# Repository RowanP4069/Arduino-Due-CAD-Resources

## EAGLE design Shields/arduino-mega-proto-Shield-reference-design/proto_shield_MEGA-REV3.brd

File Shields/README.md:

**CAD resources relating to Arduino Due shields**

*arduino-mega-proto-Shield-reference-design* - product drawings by Arduino.cc in Autodesk Eagle/Fusion360 format retreived from https://store-usa.arduino.cc/products/arduino-mega-proto-shield-rev3-pcb 2022-04-09.

*DUELib130425.lbr* - an Autocad part library by cowasaki in Autodesk Eagle/Fusion360 format retreived from https://forum.arduino.cc/t/due-shield-eagle-file/150210 2022-04-09

*Blank Shield (from mega shield)* - depopluated versions of the arduino-mega-proto-Shield in Fusion360 and Eagle board formats.

*Blank Shield (from Due)* - a depopulated version of the Arduino Due board intended as a starting point for shield design. In Fusion360 and Eagle formats.

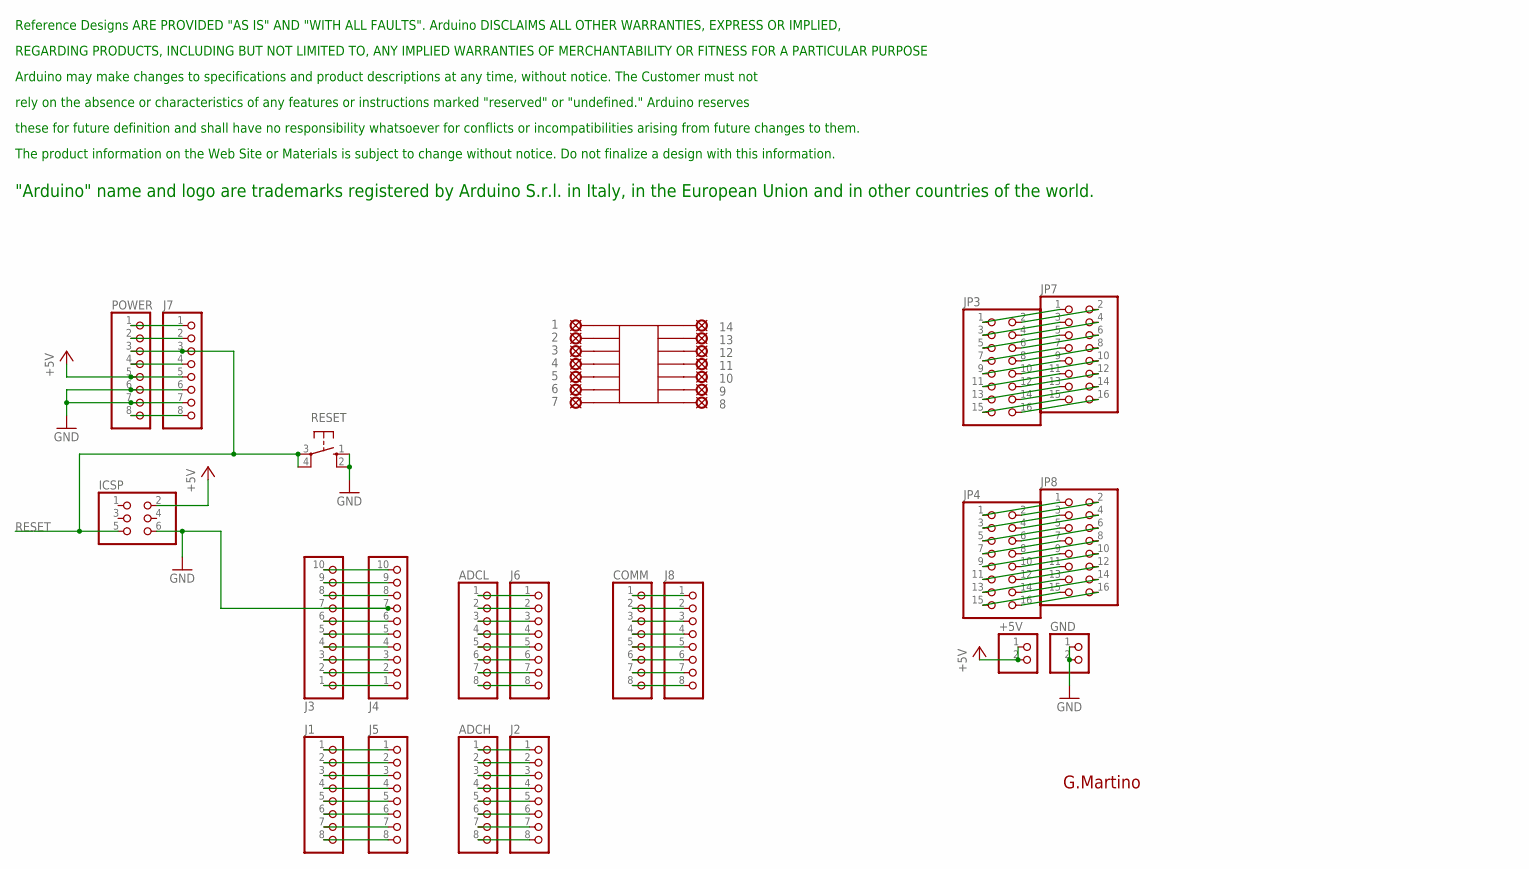
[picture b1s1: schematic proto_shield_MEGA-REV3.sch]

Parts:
1, 2, 3, 4, 5, 6, 7, 8, 9, 10, 11, 12, 13, 14: LSP10
+5V: PINHD-1X2; 1X02
ADCH: PINHD-1X8TH; 1X08-TH
ADCL: PINHD-1X8TH; 1X08-TH
COMM: PINHD-1X8TH; 1X08-TH
GND: PINHD-1X2; 1X02
IC2: SMD-14; SO-14NMW
ICSP: PINHD-2X3; 2X03
J1, J2, J5, J6, J7, J8: PINHD-1X8TH; 1X08-TH
J3, J4: PINHD-1X10TH; 1X10-TH
JP3, JP4, JP7, JP8: PINHD-2X8; 2X08
POWER: PINHD-1X8TH; 1X08-TH
RESET: 10-XX; B3F-10XX
U$1: DISCLAIMER_MINI; DISCLAIMER

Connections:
+5V: +5V.1, +5V.2, ICSP.2, J7.5, POWER.5
+9V: J7.8, POWER.8
GND: GND.1, GND.2, ICSP.6, J3.7, J4.7, J7.6, J7.7, POWER.6, POWER.7, RESET.1 (S), RESET.2 (S1)
unnamed: J3.1, J4.1
unnamed: J3.6, J4.6
unnamed: J3.4, J4.4
unnamed: J3.2, J4.2
unnamed: J3.3, J4.3
unnamed: J1.1, J5.1
unnamed: J1.2, J5.2
unnamed: J1.3, J5.3
unnamed: J1.4, J5.4
unnamed: J1.5, J5.5
unnamed: J1.6, J5.6
unnamed: J1.7, J5.7
unnamed: J1.8, J5.8
unnamed: ADCL.1, J6.1
unnamed: ADCL.2, J6.2
unnamed: ADCL.3, J6.3
unnamed: ADCL.4, J6.4
unnamed: ADCL.5, J6.5
unnamed: ADCL.6, J6.6
unnamed: 14.MP, IC2.P$14
unnamed: ADCL.7, J6.7
unnamed: ADCL.8, J6.8
unnamed: ADCH.1, J2.1
unnamed: ADCH.2, J2.2
unnamed: ADCH.3, J2.3
unnamed: 13.MP, IC2.P$13
unnamed: 12.MP, IC2.P$12
unnamed: 11.MP, IC2.P$11
unnamed: 10.MP, IC2.P$10
unnamed: 9.MP, IC2.P$9
unnamed: 8.MP, IC2.P$8
unnamed: 7.MP, IC2.P$7
unnamed: 6.MP, IC2.P$6
unnamed: 5.MP, IC2.P$5
unnamed: 3.MP, IC2.P$3
unnamed: 2.MP, IC2.P$2
unnamed: 1.MP, IC2.P$1
unnamed: 4.MP, IC2.P$4
unnamed: ADCH.4, J2.4
unnamed: ADCH.5, J2.5
unnamed: ADCH.6, J2.6
unnamed: J7.4, POWER.4
unnamed: J3.9, J4.9
unnamed: ADCH.7, J2.7
unnamed: ADCH.8, J2.8
unnamed: COMM.1, J8.1
unnamed: COMM.2, J8.2
unnamed: COMM.3, J8.3
unnamed: COMM.4, J8.4
unnamed: COMM.5, J8.5
unnamed: COMM.6, J8.6
unnamed: COMM.7, J8.7
unnamed: COMM.8, J8.8
unnamed: J3.5, J4.5
unnamed: JP3.1, JP7.1
unnamed: JP3.2, JP7.2
unnamed: JP3.3, JP7.3
unnamed: JP3.4, JP7.4
unnamed: JP3.5, JP7.5
unnamed: JP3.6, JP7.6
unnamed: JP3.7, JP7.7
unnamed: JP3.8, JP7.8
unnamed: JP3.9, JP7.9
unnamed: JP3.10, JP7.10
unnamed: JP3.11, JP7.11
unnamed: JP3.12, JP7.12
unnamed: JP3.13, JP7.13
unnamed: JP3.14, JP7.14
unnamed: JP3.15, JP7.15
unnamed: JP3.16, JP7.16
unnamed: JP4.1, JP8.1
unnamed: JP4.2, JP8.2
unnamed: JP4.3, JP8.3
unnamed: JP4.4, JP8.4
unnamed: JP4.5, JP8.5
unnamed: JP4.6, JP8.6
unnamed: JP4.7, JP8.7
unnamed: JP4.8, JP8.8
unnamed: JP4.9, JP8.9
unnamed: JP4.10, JP8.10
unnamed: JP4.11, JP8.11
unnamed: JP4.12, JP8.12
unnamed: JP4.13, JP8.13
unnamed: JP4.14, JP8.14
unnamed: JP4.15, JP8.15
unnamed: JP4.16, JP8.16
unnamed: J7.2, POWER.2
unnamed: J7.1, POWER.1
unnamed: J3.8, J4.8
unnamed: J3.10, J4.10
RESET: ICSP.5, J7.3, POWER.3, RESET.3, RESET.4 (P1)

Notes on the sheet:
G.Martino

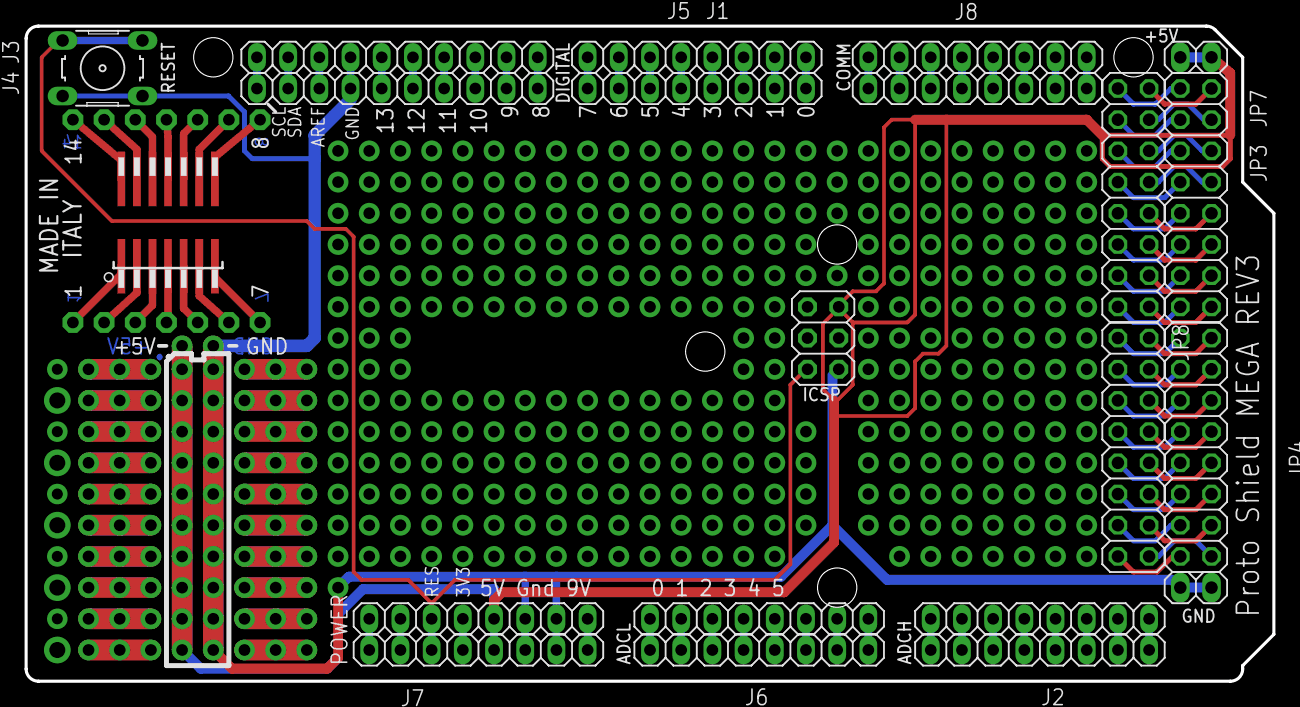
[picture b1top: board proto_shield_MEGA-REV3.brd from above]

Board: 2 copper layers, 101.6 x 53.3 mm, 36 parts (0 on the bottom side), 94 nets.

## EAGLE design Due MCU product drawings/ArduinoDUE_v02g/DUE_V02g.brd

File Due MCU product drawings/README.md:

**CAD resources related to the Due MCU**

*ArduinoDUE_v02g* - the Arduino Due MCU product drawings by Arduino.cc in Autodesk Eagle/Fusion360 format retreived from https://store-usa.arduino.cc/products/arduino-due 2022-04-09.

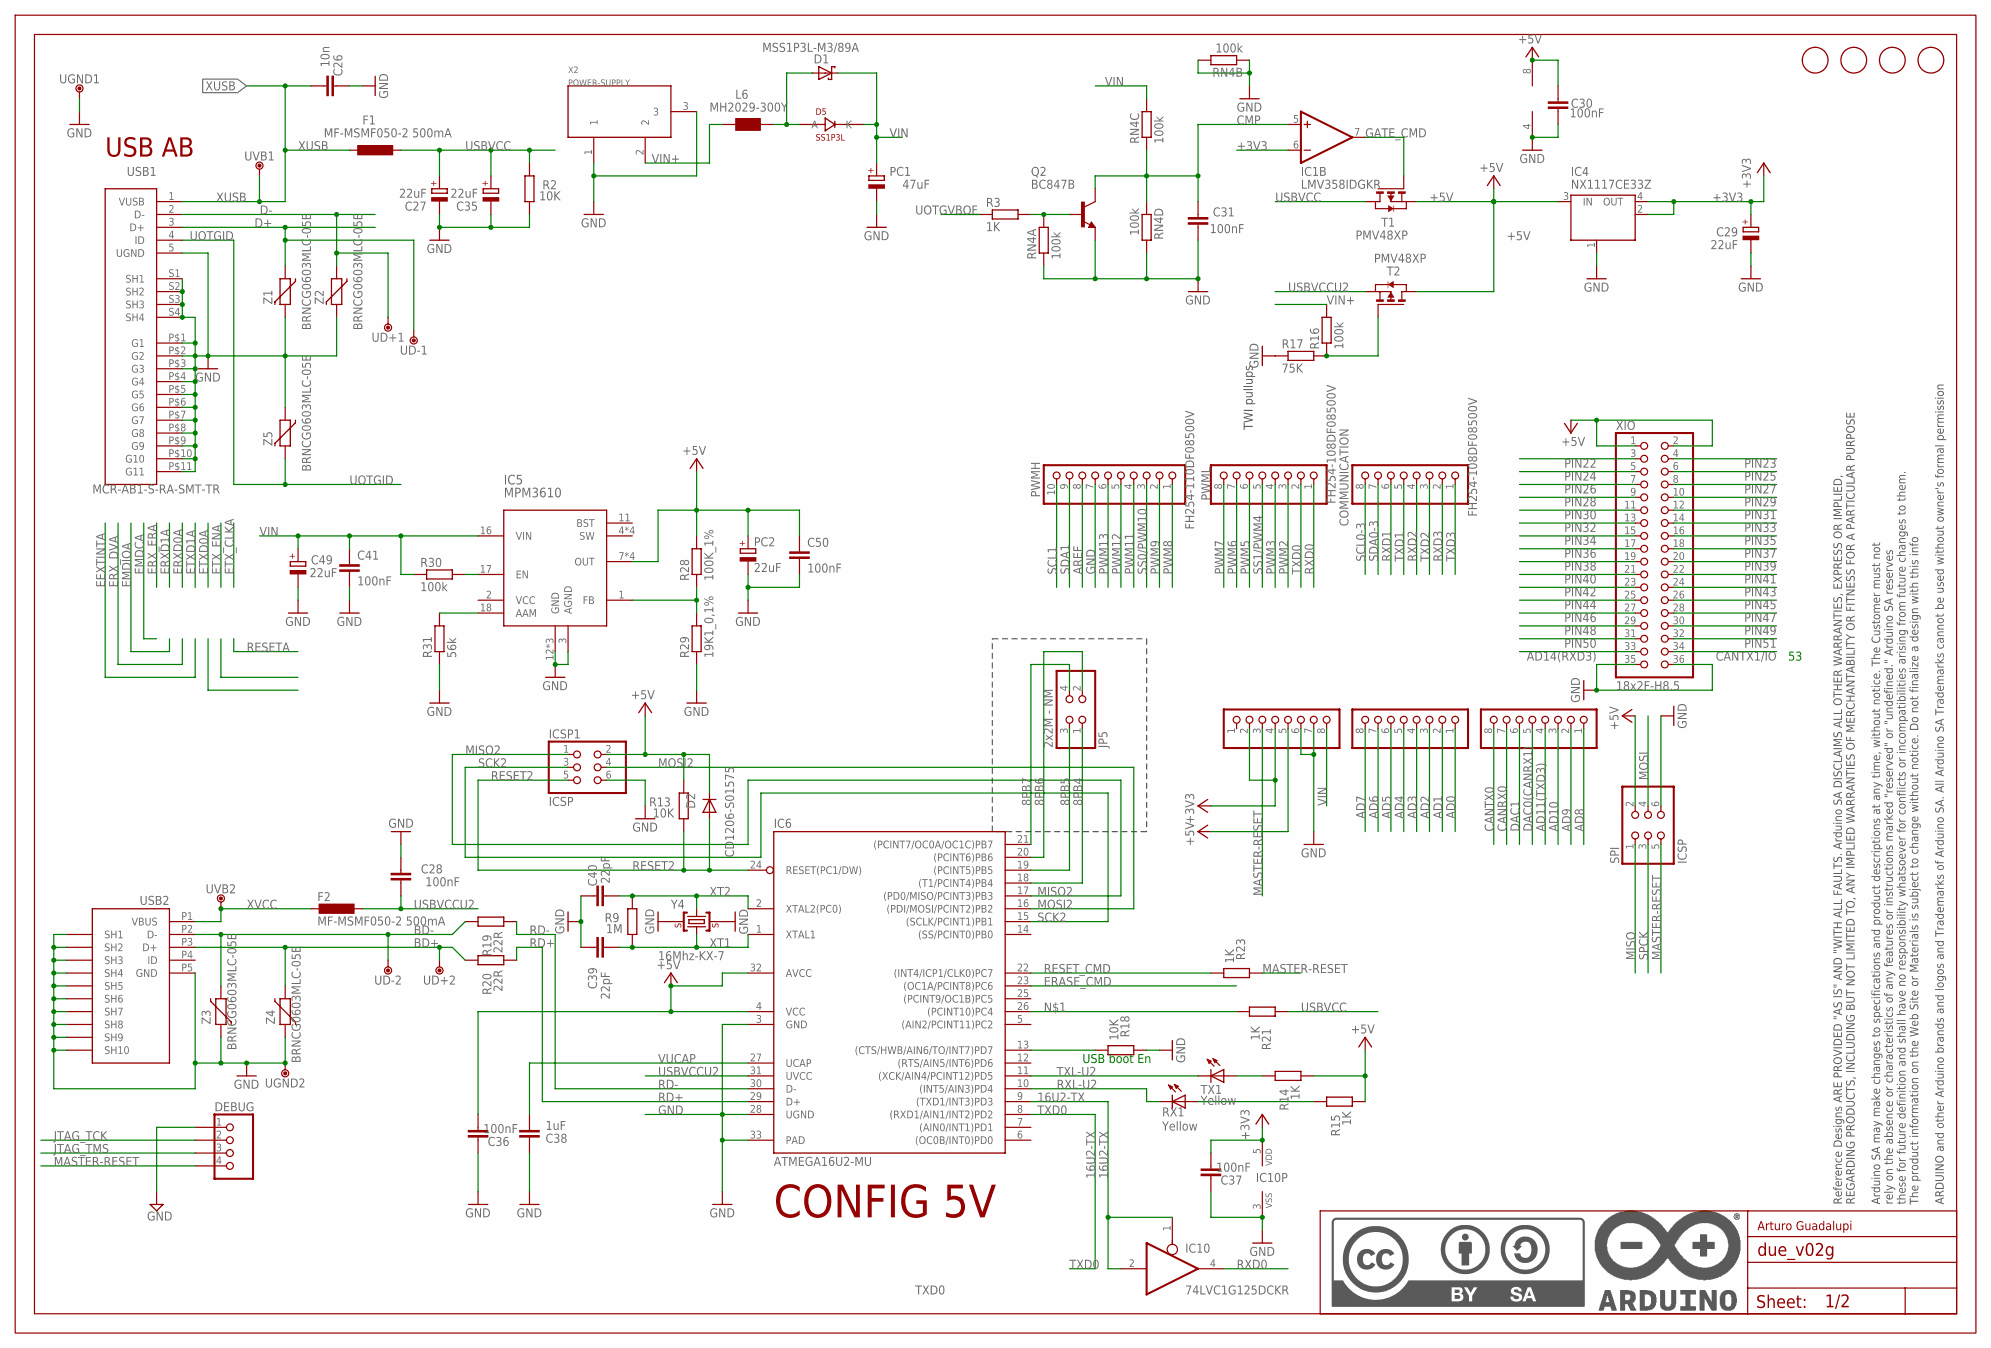
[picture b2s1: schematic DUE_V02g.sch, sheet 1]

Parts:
ADCH: FH254-108DF08500V; 1X08
ADCL: FH254-108DF08500V; 1X08
C26: 10n; C0402
C27, C29, C35, C49: 22uF; SMC_B
C28, C30, C31, C36, C37: 100nF; C0402
C38: 1uF; C0402
C39, C40: 22pF; C0402
C41, C50: 100nF; C0603-ROUND
COMMUNICATION: FH254-108DF08500V; 1X08
D1: MSS1P3L-M3/89A; MICROSMP
D2: CD1206-S01575; MINIMELF
D5: SS1P3L; DO220AAL
DEBUG: 0644_4X1VP.2,54H11,8; PH1X4-THT
F1, F2: MF-MSMF050-2 500mA; L1812
FID1, FID2, FID3, FID4: FIDUCIALMOUNT; FIDUCIA-MOUNT
IC1: LMV358IDGKR; MSOP08
IC4: NX1117CE33Z; SOT223
IC5: MPM3610; QFN-20
IC6: ATMEGA16U2-MU; MLF32
IC10: 74LVC1G125DCKR; SC70-5
ICSP1: ICSP; 2X03
JP5: 2x2M - NM; 2X02
L6: MH2029-300Y; 0805
PC1: 47uF; PANASONIC_D
PC2: 22uF; SMC_B
POWER: FH254-108DF08500V; 1X08
PWMH: FH254-110DF08500V; 1X10
PWML: FH254-108DF08500V; 1X08
Q2: BC847B; SOT23
R2, R13, R18: 10K; R0402
R3, R14, R15, R21, R23: 1K; R0402
R9: 1M; R0402
R16: 100k; R0402
R17: 75K; R0603-ROUND
R19, R20: 22R; R0402
R28: 100K_1%; R0603-ROUND
R29: 19K1_0,1%; R0603-ROUND
R30: 100k; R0603-ROUND
R31: 56k; R0603-ROUND
RN4: 100k; CAY16
RX1: Yellow; CHIPLED_0805
SPI: ICSP; 2X03
T1, T2: PMV48XP; SOT-23
TX1: Yellow; CHIPLED_0805
U$1: DNP; FRAME
UD+1, UD+2: DNP; TP-1.00MM
UD-1, UD-2: DNP; TP-1.00MM
UGND1, UGND2: DNP; TP-1.00MM
USB1: MCR-AB1-S-RA-SMT-TR; MCR-AB1-S-RA-SMT
USB2: MCR-B-S-RA-SMT-CS1TR; CON2_USB_MICRO_B_AT
UVB1, UVB2: DNP; TP-1.00MM
X2: POWER-SUPPLY; POWERSUPPLY_DC-21MM
XIO: 18x2F-H8.5; 2X18
Y4: 16Mhz-KX-7; CRYSTAL-3.2-2.5
Z1, Z2, Z3, Z4, Z5: BRNCG0603MLC-05E; CT/CN0603

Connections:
8PB4: IC6.18 ((T1/PCINT4)PB4), JP5.1
8PB5: IC6.19 ((PCINT5)PB5), JP5.3
8PB6: IC6.20 ((PCINT6)PB6), JP5.2
8PB7: IC6.21 ((PCINT7/OC0A/OC1C)PB7), JP5.4
16U2-TX: IC6.9 ((TXD1/INT3)PD3), IC10.1 (OE), IC10.2 (I)
+3V3: C29.+, C37.1, IC1.6 (-IN), IC4.2 (OUT), IC4.4 (OUT), IC10.5 (VDD), POWER.2, POWER.4; also elsewhere on the board
+5V: C30.2, C36.1, C50.1, D2.C, IC1.8 (V+), IC4.3 (IN), IC5.7 (OUT), IC5.8 (OUT), IC5.9 (OUT), IC5.20 (OUT), IC6.4 (VCC), IC6.32 (AVCC), ICSP1.2, PC2.+, POWER.5, R13.2, R14.1, R15.1, R28.2, SPI.2, T1.2 (S), T2.1 (D), XIO.1, XIO.2
AD0: ADCL.1; also elsewhere on the board
AD1: ADCL.2; also elsewhere on the board
AD2: ADCL.3; also elsewhere on the board
AD3: ADCL.4; also elsewhere on the board
AD4: ADCL.5; also elsewhere on the board
AD5: ADCL.6; also elsewhere on the board
AD6: ADCL.7; also elsewhere on the board
AD7: ADCL.8; also elsewhere on the board
AD8: ADCH.1; also elsewhere on the board
AD9: ADCH.2; also elsewhere on the board
AD10: ADCH.3; also elsewhere on the board
AD11(TXD3): ADCH.4; also elsewhere on the board
AD14(RXD3): XIO.33; also elsewhere on the board
AREF: PWMH.8; also elsewhere on the board
BD+: R20.2, UD+2.X, USB2.P3 (D+), Z4.2
BD-: R19.2, UD-2.X, USB2.P2 (D-), Z3.2
CANRX0: ADCH.7; also elsewhere on the board
CANTX0: ADCH.8; also elsewhere on the board
CANTX1/IO: XIO.34; also elsewhere on the board
CMP: C31.2, IC1.5 (+IN), Q2.3 (C), RN4.3 (1), RN4.4 (1)
D+: UD-1.X, USB1.3 (D+), Z1.1; also elsewhere on the board
D-: UD+1.X, USB1.2 (D-), Z2.1; also elsewhere on the board
DAC0(CANRX1): ADCH.5; also elsewhere on the board
DAC1: ADCH.6; also elsewhere on the board
DTR: IC6.13 ((CTS/HWB/AIN6/TO/INT7)PD7), R18.1
ERASE_CMD: IC6.23 ((OC1A/PCINT8)PC6); also elsewhere on the board
GATE_CMD: IC1.7 (OUT), T1.3 (G)
GND: C26.2, C27.-, C28.2, C29.-, C30.1, C31.1, C35.-, C36.2, C37.2, C38.2, C39.2, C40.2, C41.2, C49.-, C50.2, DEBUG.1, IC1.4 (V-), IC4.1 (GND/ADJ), IC5.3 (AGND), IC5.12 (GND), IC5.13 (GND), IC5.14 (GND), IC6.3 (GND), IC6.28 (UGND), IC6.33 (PAD), IC10.3 (VSS), ICSP1.6, PC1.-, PC2.-, POWER.6, POWER.7, PWMH.7, Q2.2 (E), R2.1, R17.1, R18.2, R29.1, R31.1, RN4.1, RN4.2 (1), RN4.5 (2), RN4.7 (2), SPI.6, UGND1.X, UGND2.X, USB1.5 (UGND), USB1.P$1 (G1), USB1.P$2 (G2), USB1.P$3 (G3), USB1.P$4 (G4), USB1.P$5 (G5), USB1.P$6 (G6), USB1.P$7 (G7), USB1.P$8 (G8), USB1.P$9 (G9), USB1.P$10 (G10), USB1.P$11 (G11), USB1.S1 (SH1), USB1.S2 (SH2), USB1.S3 (SH3), USB1.S4 (SH4), USB2.P5 (GND), USB2.P$1 (SH7), USB2.P$2 (SH8), USB2.P$3 (SH9), USB2.P$4 (SH10), USB2.P$5 (SH7), USB2.P$6 (SH8), USB2.P$7 (SH9), USB2.P$8 (SH10), USB2.S1 (SH1), USB2.S2 (SH2), USB2.S3 (SH3), USB2.S4 (SH4), USB2.S5 (SH5), USB2.S6 (SH6), X2.1, X2.3, XIO.35, XIO.36, Y4.2 (GND), Y4.4 (GND), Z1.2, Z2.2, Z3.1, Z4.1, Z5.1; also elsewhere on the board
JTAG_TCK: DEBUG.2; also elsewhere on the board
JTAG_TMS: DEBUG.3; also elsewhere on the board
MASTER-RESET: DEBUG.4, POWER.3, R23.2, SPI.5; also elsewhere on the board
MISO: SPI.1; also elsewhere on the board
MISO2: IC6.17 ((PD0/MISO/PCINT3)PB3), ICSP1.1
MOSI: SPI.4; also elsewhere on the board
MOSI2: IC6.16 ((PDI/MOSI/PCINT2)PB2), ICSP1.4
unnamed: IC6.26 ((PCINT10)PC4), R21.1
unnamed: R15.2, RX1.A
unnamed: Q2.1 (B), R3.2, RN4.8 (2)
unnamed: D1.A, D5.P$2 (A), L6.1
unnamed: R14.2, TX1.A
unnamed: R16.1, R17.2, T2.3 (G)
unnamed: IC5.1 (FB), R28.1, R29.2
unnamed: IC5.17 (EN), R30.2
unnamed: IC5.18 (AAM), R31.2
PIN22: XIO.3; also elsewhere on the board
PIN23: XIO.4; also elsewhere on the board
PIN24: XIO.5; also elsewhere on the board
PIN25: XIO.6; also elsewhere on the board
PIN26: XIO.7; also elsewhere on the board
PIN27: XIO.8; also elsewhere on the board
PIN28: XIO.9; also elsewhere on the board
PIN29: XIO.10; also elsewhere on the board
PIN30: XIO.11; also elsewhere on the board
PIN31: XIO.12; also elsewhere on the board
PIN32: XIO.13; also elsewhere on the board
PIN33: XIO.14; also elsewhere on the board
PIN34: XIO.15; also elsewhere on the board
PIN35: XIO.16; also elsewhere on the board
PIN36: XIO.17; also elsewhere on the board
PIN37: XIO.18; also elsewhere on the board
PIN38: XIO.19; also elsewhere on the board
PIN39: XIO.20; also elsewhere on the board
PIN40: XIO.21; also elsewhere on the board
PIN41: XIO.22; also elsewhere on the board
PIN42: XIO.23; also elsewhere on the board
PIN43: XIO.24; also elsewhere on the board
PIN44: XIO.25; also elsewhere on the board
PIN45: XIO.26; also elsewhere on the board
PIN46: XIO.27; also elsewhere on the board
PIN47: XIO.28; also elsewhere on the board
PIN48: XIO.29; also elsewhere on the board
PIN49: XIO.30; also elsewhere on the board
PIN50: XIO.31; also elsewhere on the board
PIN51: XIO.32; also elsewhere on the board
PWM2: PWML.3; also elsewhere on the board
PWM3: PWML.4; also elsewhere on the board
PWM5: PWML.6; also elsewhere on the board
PWM6: PWML.7; also elsewhere on the board
PWM7: PWML.8; also elsewhere on the board
PWM8: PWMH.1; also elsewhere on the board
PWM9: PWMH.2; also elsewhere on the board
PWM11: PWMH.4; also elsewhere on the board
PWM12: PWMH.5; also elsewhere on the board
PWM13: PWMH.6; also elsewhere on the board
RD+: IC6.29 (D+), R20.1
RD-: IC6.30 (D-), R19.1
RESET2: D2.A, IC6.24 (RESET(PC1/DW)), ICSP1.5, R13.1
RESET_CMD: IC6.22 ((INT4/ICP1/CLK0)PC7), R23.1
RXD0: IC10.4 (O), PWML.1; also elsewhere on the board
RXD1: COMMUNICATION.6; also elsewhere on the board
RXD2: COMMUNICATION.4; also elsewhere on the board
RXD3: COMMUNICATION.2; also elsewhere on the board
RXL-U2: IC6.10 ((INT5/AIN3)PD4), RX1.C
SCK2: IC6.15 ((SCLK/PCINT1)PB1), ICSP1.3
SCL0-3: COMMUNICATION.8; also elsewhere on the board
SCL1: PWMH.10; also elsewhere on the board
SDA0-3: COMMUNICATION.7; also elsewhere on the board
SDA1: PWMH.9; also elsewhere on the board
SPCK: SPI.3; also elsewhere on the board
SS0/PWM10: PWMH.3; also elsewhere on the board
SS1/PWM4: PWML.5; also elsewhere on the board
TXD0: IC6.8 ((RXD1/AIN1/INT2)PD2), PWML.2; also elsewhere on the board
TXD1: COMMUNICATION.5; also elsewhere on the board
TXD2: COMMUNICATION.3; also elsewhere on the board
TXD3: COMMUNICATION.1; also elsewhere on the board
TXL-U2: IC6.11 ((XCK/AIN4/PCINT12)PD5), TX1.C
UOTGID: USB1.4 (ID), Z5.2; also elsewhere on the board
UOTGVBOF: R3.1; also elsewhere on the board
USBVCC: C27.+, C35.+, F1.1, R2.2, R21.2, T1.1 (D)
USBVCCU2: C28.1, F2.1, IC6.31 (UVCC), T2.2 (S)
VIN: C41.1, C49.+, D1.K (C), D5.P$1 (K), IC5.16 (VIN), PC1.+, POWER.8, R30.1, RN4.6 (2)
VIN+: L6.2, R16.2, X2.2
VUCAP: C38.1, IC6.27 (UCAP)
XT1: C39.1, IC6.1 (XTAL1), R9.1, Y4.1 (C1)
XT2: C40.1, IC6.2 (XTAL2(PC0)), R9.2, Y4.3 (C2)
XUSB: C26.1, F1.2, USB1.1 (VUSB), UVB1.X; also elsewhere on the board
XVCC: F2.2, USB2.P1 (VBUS), UVB2.X

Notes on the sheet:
TWI pullups
USB AB
USB boot En
CONFIG 5V
Arturo Guadalupi

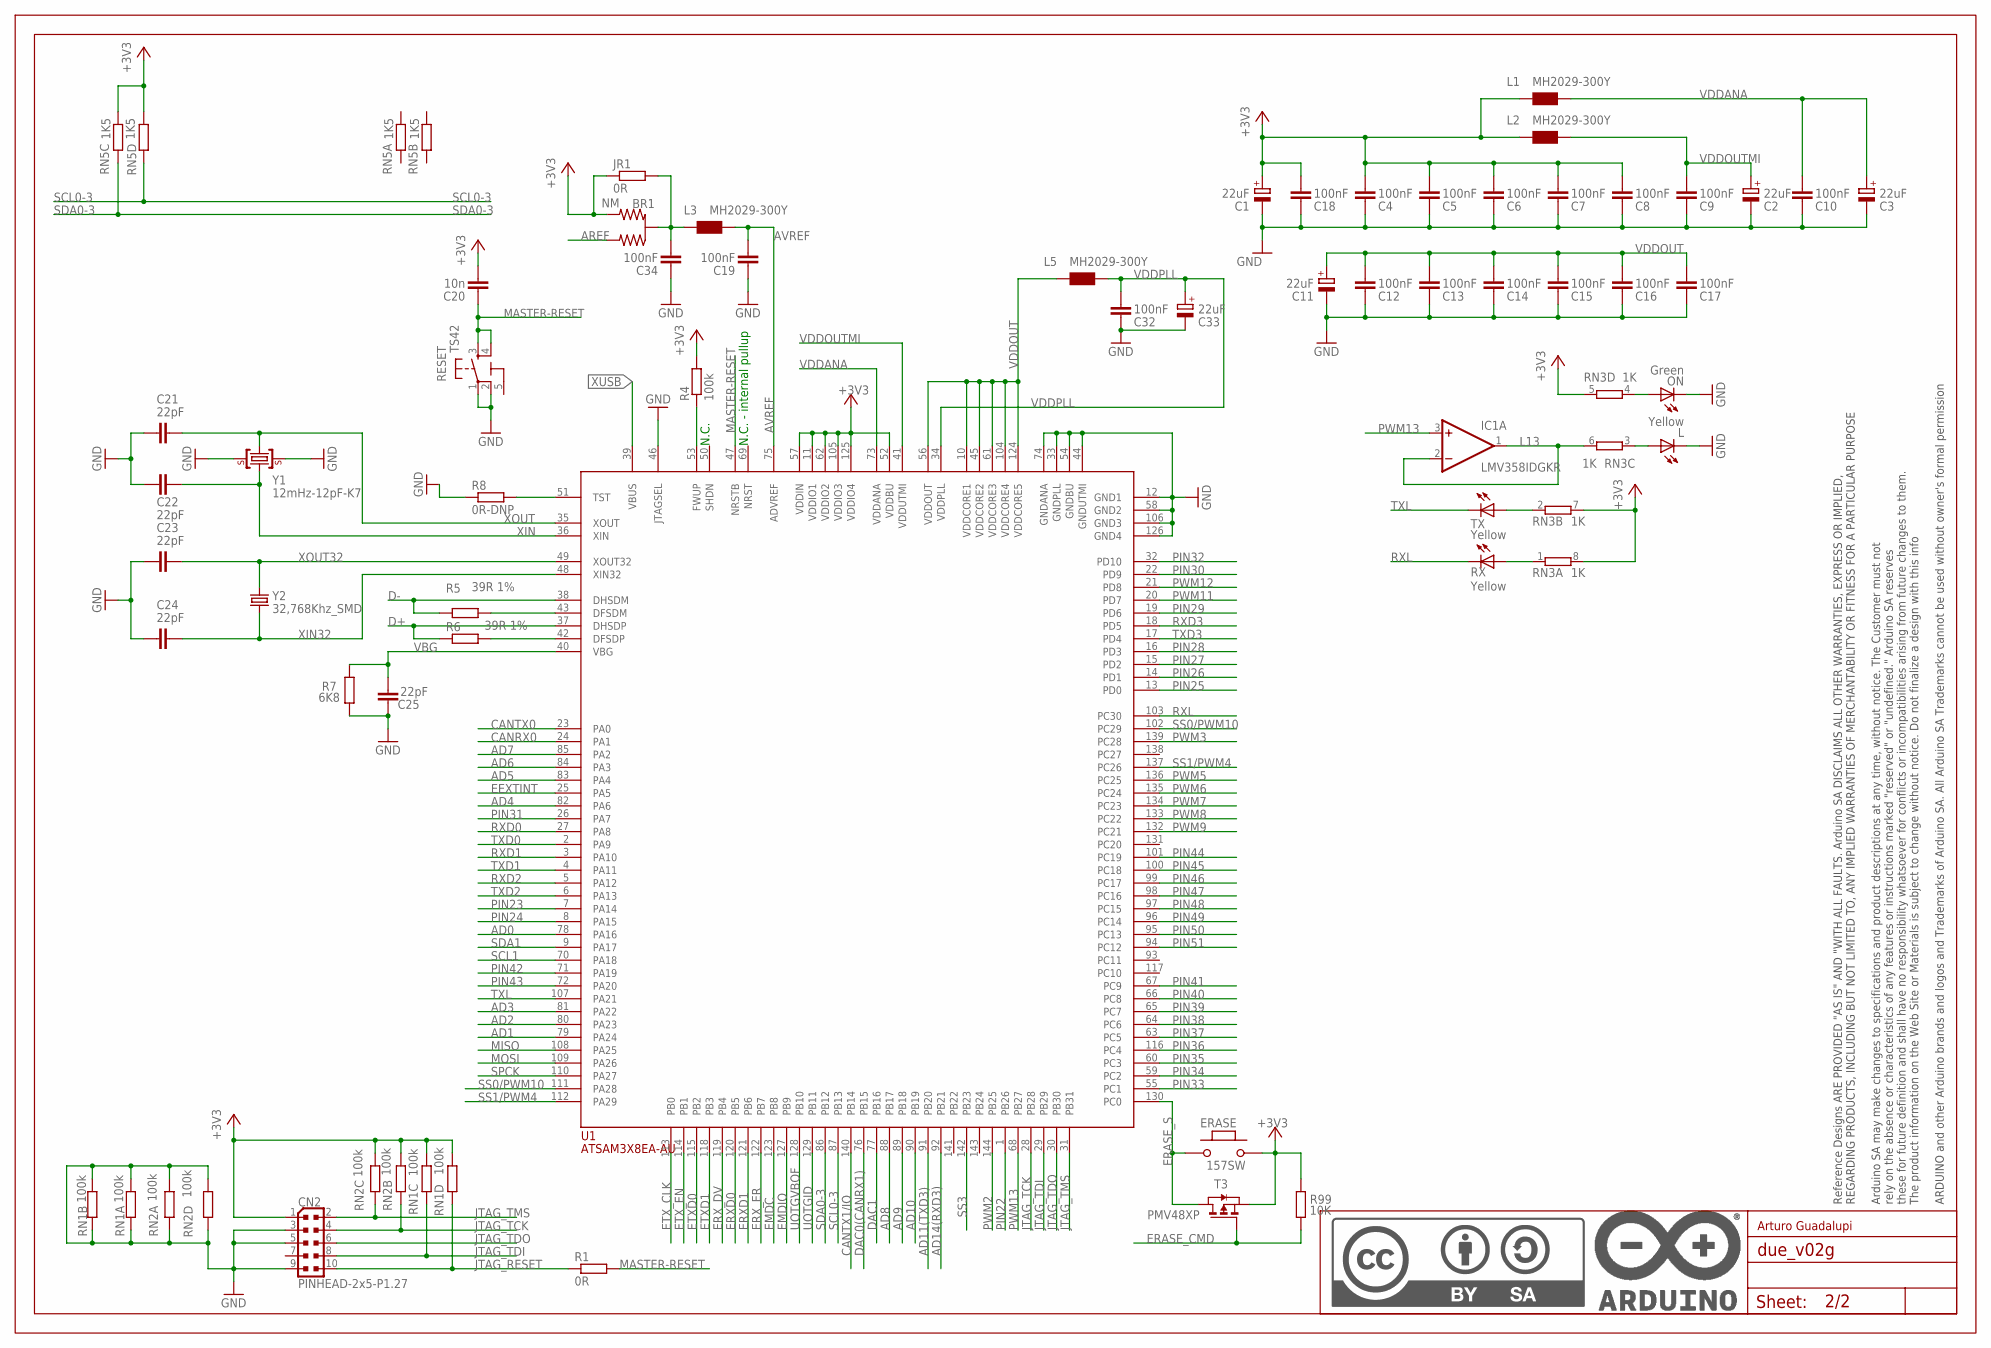
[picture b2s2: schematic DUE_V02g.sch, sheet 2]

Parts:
BR1: NM; J0402
C1, C2, C3, C11, C33: 22uF; SMC_B
C4, C5, C6, C7, C8, C9, C10, C12, C13, C14, C15, C16, C17, C18, C19, C32, C34: 100nF; C0402
C20: 10n; C0402
C21, C22, C23, C24, C25: 22pF; C0402
CN2: PINHEAD-2x5-P1.27; PINHEAD_2X05_127
ERASE: 157SW; SMD_157SW
IC1: LMV358IDGKR; MSOP08
JR1: 0R; R0402
L: Yellow; CHIPLED_0805
L1, L2, L3, L5: MH2029-300Y; 0805
ON: Green; CHIPLED_0805
R1: 0R; R0402
R4: 100k; R0402
R5, R6: 39R 1%; R0402
R7: 6K8; R0603-ROUND
R8: 0R-DNP; R0402
R99: 10K; R0402
RESET: TS42
RN1, RN2: 100k; CAY16
RN3: 1K; CAY16
RN5: 1K5; CAY16
RX: Yellow; CHIPLED_0805
T3: PMV48XP; SOT-23
TX: Yellow; CHIPLED_0805
U1: ATSAM3X8EA-AU; LQFP144
U$2: DNP; FRAME
Y1: 12mHz-12pF-K7; CRYSTAL-3.2-2.5
Y2: 32,768Khz_SMD; RESONATOR_EPSON_FC_145

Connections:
5-GND: RESET.5 (5-GND)
+3V3: BR1.3 (2), C1.+, C4.2, C5.2, C6.2, C7.2, C8.2, C18.2, C20.2, CN2.1, ERASE.1, JR1.1, L1.1, L2.1, R4.2, R99.2, RN1.5 (2), RN1.6 (2), RN2.2 (1), RN2.3 (1), RN3.5 (2), RN3.7 (2), RN3.8 (2), RN5.3 (1), RN5.4 (1), T3.2 (S), U1.11 (VDDIO1), U1.52 (VDDBU), U1.57 (VDDIN), U1.62 (VDDIO2), U1.105 (VDDIO3), U1.125 (VDDIO4); also elsewhere on the board
AD0: U1.78 (PA16); also elsewhere on the board
AD1: U1.79 (PA24); also elsewhere on the board
AD2: U1.80 (PA23); also elsewhere on the board
AD3: U1.81 (PA22); also elsewhere on the board
AD4: U1.82 (PA6); also elsewhere on the board
AD5: U1.83 (PA4); also elsewhere on the board
AD6: U1.84 (PA3); also elsewhere on the board
AD7: U1.85 (PA2); also elsewhere on the board
AD8: U1.88 (PB17); also elsewhere on the board
AD9: U1.89 (PB18); also elsewhere on the board
AD10: U1.90 (PB19); also elsewhere on the board
AD11(TXD3): U1.91 (PB20); also elsewhere on the board
AD14(RXD3): U1.92 (PB21); also elsewhere on the board
AREF: BR1.1; also elsewhere on the board
AVREF: C19.2, L3.2, U1.75 (ADVREF)
AVREFL: BR1.2 (C), C34.2, JR1.2, L3.1
CANRX0: U1.24 (PA1); also elsewhere on the board
CANTX0: U1.23 (PA0); also elsewhere on the board
CANTX1/IO: U1.140 (PB14); also elsewhere on the board
D+: R6.1, U1.37 (DHSDP); also elsewhere on the board
D-: R5.1, U1.38 (DHSDM); also elsewhere on the board
DAC0(CANRX1): U1.76 (PB15); also elsewhere on the board
DAC1: U1.77 (PB16); also elsewhere on the board
EEXTINT: U1.25 (PA5)
EMDC: U1.123 (PB8)
EMDIO: U1.127 (PB9)
ERASE_CMD: R99.1, T3.3 (G); also elsewhere on the board
ERASE_S: ERASE.2, T3.1 (D), U1.130 (PC0)
ERXD0: U1.120 (PB5)
ERXD1: U1.121 (PB6)
ERX_DV: U1.119 (PB4)
ERX_ER: U1.122 (PB7)
ETXD0: U1.115 (PB2)
ETXD1: U1.118 (PB3)
ETX_CLK: U1.113 (PB0)
ETX_EN: U1.114 (PB1)
GND: C1.-, C2.-, C3.-, C4.1, C5.1, C6.1, C7.1, C8.1, C9.1, C10.1, C11.-, C12.1, C13.1, C14.1, C15.1, C16.1, C17.1, C18.1, C19.1, C21.2, C22.2, C23.2, C24.2, C25.2, C32.1, C33.-, C34.1, CN2.3, CN2.5, CN2.9, L.C, ON.C, R7.1, R8.1, RESET.1, RESET.2, RN1.1, RN1.2 (1), RN1.7 (2), RN1.8 (2), RN2.1, RN2.4 (1), RN2.5 (2), RN2.8 (2), U1.12 (GND1), U1.33 (GNDPLL), U1.44 (GNDUTMI), U1.46 (JTAGSEL), U1.54 (GNDBU), U1.58 (GND2), U1.74 (GNDANA), U1.106 (GND3), U1.126 (GND4), Y1.2 (GND), Y1.4 (GND); also elsewhere on the board
JTAG_RESET: CN2.10, R1.1, RN1.4 (1)
JTAG_TCK: CN2.4, RN2.7 (2), U1.28 (PB28); also elsewhere on the board
JTAG_TDI: CN2.8, RN1.3 (1), U1.29 (PB29)
JTAG_TDO: CN2.6, U1.30 (PB30)
JTAG_TMS: CN2.2, RN2.6 (2), U1.31 (PB31); also elsewhere on the board
L13: IC1.1 (OUT), IC1.2 (-IN), RN3.6 (2)
MASTER-RESET: C20.1, R1.2, RESET.3, RESET.4, U1.47 (NRSTB); also elsewhere on the board
MISO: U1.108 (PA25); also elsewhere on the board
MOSI: U1.109 (PA26); also elsewhere on the board
unnamed: L.A, RN3.3 (1)
unnamed: ON.A, RN3.4 (1)
unnamed: R8.2, U1.51 (TST)
unnamed: R4.1, U1.53 (FWUP)
unnamed: R5.2, U1.43 (DFSDM)
unnamed: R6.2, U1.42 (DFSDP)
unnamed: RN3.1, RX.A
unnamed: RN3.2 (1), TX.A
PIN22: U1.1 (PB26); also elsewhere on the board
PIN23: U1.7 (PA14); also elsewhere on the board
PIN24: U1.8 (PA15); also elsewhere on the board
PIN25: U1.13 (PD0); also elsewhere on the board
PIN26: U1.14 (PD1); also elsewhere on the board
PIN27: U1.15 (PD2); also elsewhere on the board
PIN28: U1.16 (PD3); also elsewhere on the board
PIN29: U1.19 (PD6); also elsewhere on the board
PIN30: U1.22 (PD9); also elsewhere on the board
PIN31: U1.26 (PA7); also elsewhere on the board
PIN32: U1.32 (PD10); also elsewhere on the board
PIN33: U1.55 (PC1); also elsewhere on the board
PIN34: U1.59 (PC2); also elsewhere on the board
PIN35: U1.60 (PC3); also elsewhere on the board
PIN36: U1.116 (PC4); also elsewhere on the board
PIN37: U1.63 (PC5); also elsewhere on the board
PIN38: U1.64 (PC6); also elsewhere on the board
PIN39: U1.65 (PC7); also elsewhere on the board
PIN40: U1.66 (PC8); also elsewhere on the board
PIN41: U1.67 (PC9); also elsewhere on the board
PIN42: U1.71 (PA19); also elsewhere on the board
PIN43: U1.72 (PA20); also elsewhere on the board
PIN44: U1.101 (PC19); also elsewhere on the board
PIN45: U1.100 (PC18); also elsewhere on the board
PIN46: U1.99 (PC17); also elsewhere on the board
PIN47: U1.98 (PC16); also elsewhere on the board
PIN48: U1.97 (PC15); also elsewhere on the board
PIN49: U1.96 (PC14); also elsewhere on the board
PIN50: U1.95 (PC13); also elsewhere on the board
PIN51: U1.94 (PC12); also elsewhere on the board
PWM2: U1.144 (PB25); also elsewhere on the board
PWM3: U1.139 (PC28); also elsewhere on the board
PWM5: U1.136 (PC25); also elsewhere on the board
PWM6: U1.135 (PC24); also elsewhere on the board
PWM7: U1.134 (PC23); also elsewhere on the board
PWM8: U1.133 (PC22); also elsewhere on the board
PWM9: U1.132 (PC21); also elsewhere on the board
PWM11: U1.20 (PD7); also elsewhere on the board
PWM12: U1.21 (PD8); also elsewhere on the board
PWM13: IC1.3 (+IN), U1.68 (PB27); also elsewhere on the board
RXD0: U1.27 (PA8); also elsewhere on the board
RXD1: U1.3 (PA10); also elsewhere on the board
RXD2: U1.5 (PA12); also elsewhere on the board
RXD3: U1.18 (PD5); also elsewhere on the board
RXL: RX.C, U1.103 (PC30)
SCL0-3: RN5.5 (2), U1.87 (PB13); also elsewhere on the board
SCL1: U1.70 (PA18); also elsewhere on the board
SDA0-3: RN5.6 (2), U1.86 (PB12); also elsewhere on the board
SDA1: U1.9 (PA17); also elsewhere on the board
SPCK: U1.110 (PA27); also elsewhere on the board
SS0/PWM10: U1.102 (PC29), U1.111 (PA28); also elsewhere on the board
SS1/PWM4: U1.112 (PA29), U1.137 (PC26); also elsewhere on the board
SS3: U1.142 (PB23)
TXD0: U1.2 (PA9); also elsewhere on the board
TXD1: U1.4 (PA11); also elsewhere on the board
TXD2: U1.6 (PA13); also elsewhere on the board
TXD3: U1.17 (PD4); also elsewhere on the board
TXL: TX.C, U1.107 (PA21)
UOTGID: U1.129 (PB11); also elsewhere on the board
UOTGVBOF: U1.128 (PB10); also elsewhere on the board
VBG: C25.1, R7.2, U1.40 (VBG)
VDDANA: C3.+, C10.2, L1.2, U1.73 (VDDANA)
VDDOUT: C11.+, C12.2, C13.2, C14.2, C15.2, C16.2, C17.2, L5.1, U1.10 (VDDCORE1), U1.45 (VDDCORE2), U1.56 (VDDOUT), U1.61 (VDDCORE3), U1.104 (VDDCORE4), U1.124 (VDDCORE5)
VDDOUTMI: C2.+, C9.2, L2.2, U1.41 (VDDUTMI)
VDDPLL: C32.2, C33.+, L5.2, U1.34 (VDDPLL)
XIN: C22.1, U1.36 (XIN), Y1.1 (C1)
XIN32: C24.1, U1.48 (XIN32), Y2.P$2 (2)
XOUT: C21.1, U1.35 (XOUT), Y1.3 (C2)
XOUT32: C23.1, U1.49 (XOUT32), Y2.P$1 (1)
XUSB: U1.39 (VBUS); also elsewhere on the board

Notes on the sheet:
N.C.
N.C. - internal pullup
Arturo Guadalupi

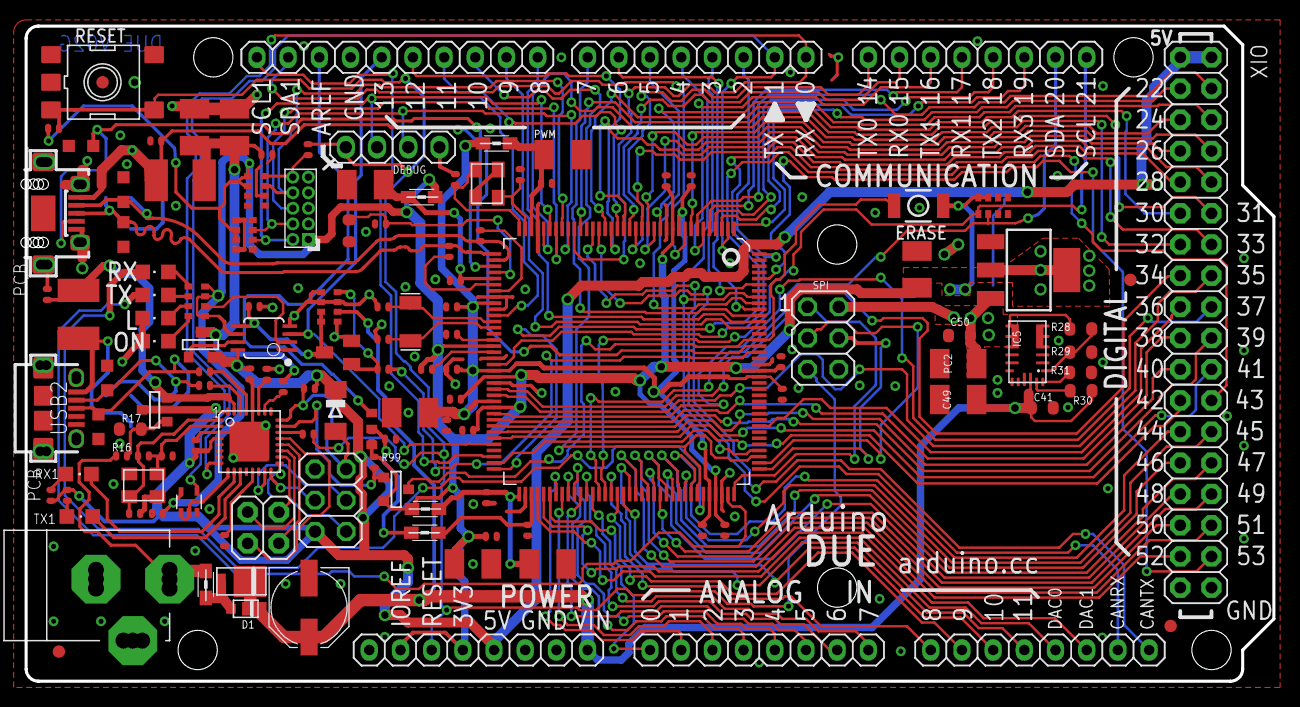
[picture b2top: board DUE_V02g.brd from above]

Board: 2 copper layers, 101.6 x 53.3 mm, 141 parts (0 on the bottom side), 150 nets.

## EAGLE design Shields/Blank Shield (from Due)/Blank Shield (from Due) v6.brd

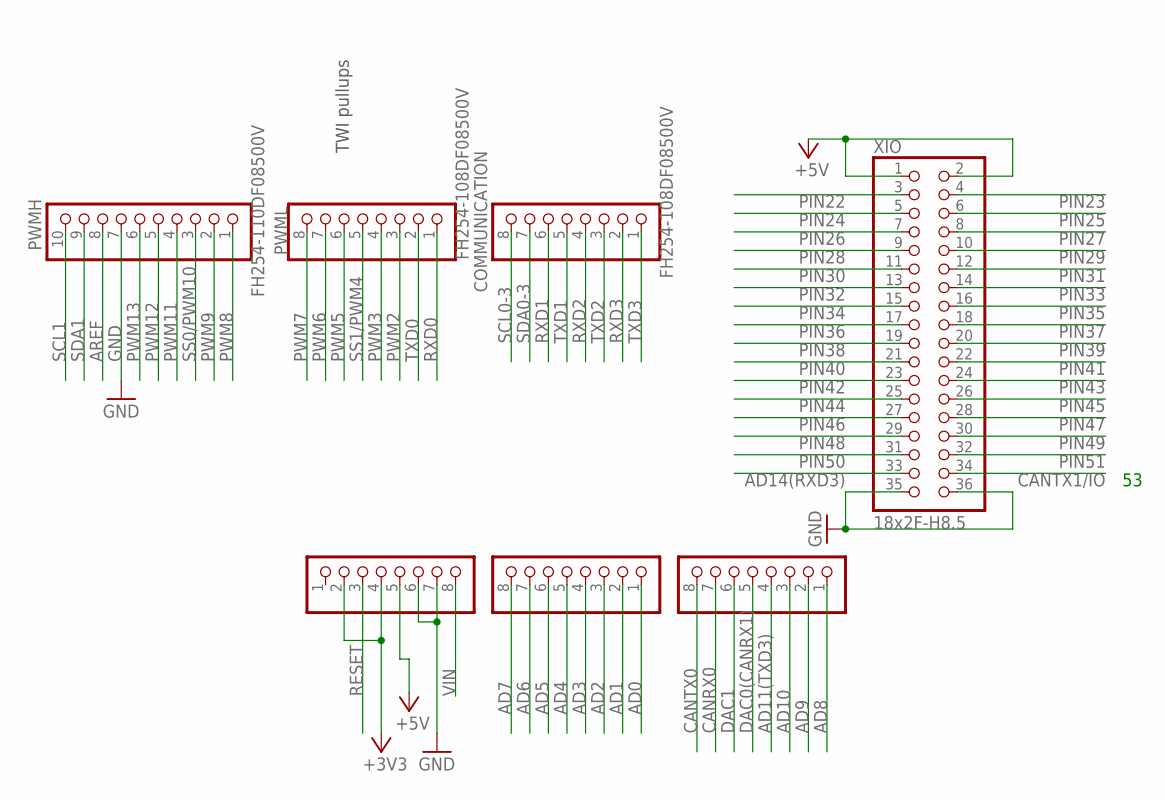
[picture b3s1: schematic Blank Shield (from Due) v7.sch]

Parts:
ADCH: FH254-108DF08500V; 1X08
ADCL: FH254-108DF08500V; 1X08
COMMUNICATION: FH254-108DF08500V; 1X08
POWER: FH254-108DF08500V; 1X08
PWMH: FH254-110DF08500V; 1X10
PWML: FH254-108DF08500V; 1X08
XIO: 18x2F-H8.5; 2X18

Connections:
+3V3: POWER.2, POWER.4
+5V: POWER.5, XIO.1, XIO.2
AD0: ADCL.1
AD1: ADCL.2
AD2: ADCL.3
AD3: ADCL.4
AD4: ADCL.5
AD5: ADCL.6
AD6: ADCL.7
AD7: ADCL.8
AD8: ADCH.1
AD9: ADCH.2
AD10: ADCH.3
AD11(TXD3): ADCH.4
AD14(RXD3): XIO.33
AREF: PWMH.8
CANRX0: ADCH.7
CANTX0: ADCH.8
CANTX1/IO: XIO.34
DAC0(CANRX1): ADCH.5
DAC1: ADCH.6
GND: POWER.6, POWER.7, PWMH.7, XIO.35, XIO.36
PIN22: XIO.3
PIN23: XIO.4
PIN24: XIO.5
PIN25: XIO.6
PIN26: XIO.7
PIN27: XIO.8
PIN28: XIO.9
PIN29: XIO.10
PIN30: XIO.11
PIN31: XIO.12
PIN32: XIO.13
PIN33: XIO.14
PIN34: XIO.15
PIN35: XIO.16
PIN36: XIO.17
PIN37: XIO.18
PIN38: XIO.19
PIN39: XIO.20
PIN40: XIO.21
PIN41: XIO.22
PIN42: XIO.23
PIN43: XIO.24
PIN44: XIO.25
PIN45: XIO.26
PIN46: XIO.27
PIN47: XIO.28
PIN48: XIO.29
PIN49: XIO.30
PIN50: XIO.31
PIN51: XIO.32
PWM2: PWML.3
PWM3: PWML.4
PWM5: PWML.6
PWM6: PWML.7
PWM7: PWML.8
PWM8: PWMH.1
PWM9: PWMH.2
PWM11: PWMH.4
PWM12: PWMH.5
PWM13: PWMH.6
RXD0: PWML.1
RXD1: COMMUNICATION.6
RXD2: COMMUNICATION.4
RXD3: COMMUNICATION.2
SCL0-3: COMMUNICATION.8
SCL1: PWMH.10
SDA0-3: COMMUNICATION.7
SDA1: PWMH.9
SS0/PWM10: PWMH.3
SS1/PWM4: PWML.5
TXD0: PWML.2
TXD1: COMMUNICATION.5
TXD2: COMMUNICATION.3
TXD3: COMMUNICATION.1
VIN: POWER.8

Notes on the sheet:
TWI pullups

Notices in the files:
parts and their libraries:
Arduino-utility: Copyright (c) 2016-2017 Arduino LLC.  All right reserved.
